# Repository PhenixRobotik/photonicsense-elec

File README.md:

# ultraphotonicsense-elec
Board for Time of Flight and ultrasonic sensors management

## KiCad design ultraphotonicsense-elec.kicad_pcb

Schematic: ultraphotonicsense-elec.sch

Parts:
C1, C2, C18, C19: 100n; C_0805_2012Metric_Pad1.15x1.40mm_HandSolder
J1: Conn_Debug; JST_PH_B6B-PH-K_1x06_P2.00mm_Vertical
JP1: Jumper_NC_Dual; PinHeader_1x03_P2.54mm_Vertical
LOGO1: Logo_Open_Hardware_Small; Logo_16,9mm
LOGO2: Logo_Open_Hardware_Small; OSHW-Logo2_7.3x6mm_SilkScreen
LOGO3: Logo_Open_Hardware_Small; KiCad-Logo_6mm_SilkScreen
MH1, MH2, MH3, MH4: MountingHole_Pad; MountingHole_2.2mm_M2_Pad
R1: 10k; R_0805_2012Metric_Pad1.15x1.40mm_HandSolder
U1: TXB0108PW; TSSOP-20_4.4x6.5mm_P0.65mm
U2: 74HC164; SOIC-14_3.9x8.7mm_P1.27mm
U8: TXB0104PW; TSSOP-14_4.4x5mm_P0.65mm

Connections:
+2V8: C19.2, U2.14, U8.1, U8.8; also elsewhere on the board
+3V3: C1.1, C18.2, JP1.3, U1.2, U8.14; also elsewhere on the board
+5V: JP1.1; also elsewhere on the board
/NRST_Logic/NRST: U8.11; also elsewhere on the board
/NRST_Logic/NRST_DBG: J1.2; also elsewhere on the board
/STM32F303K8/SWCLK: J1.3; also elsewhere on the board
/STM32F303K8/SWDIO: J1.4; also elsewhere on the board
/STM32F303K8/TOF_RESET_DATA: U8.13; also elsewhere on the board
/STM32F303K8/TOF_RESET_SHIFT: U8.12; also elsewhere on the board
/STM32F303K8/UART_RX: J1.5; also elsewhere on the board
/STM32F303K8/UART_TX: J1.6; also elsewhere on the board
/STM32F303K8/US_ECHO_0: U1.8; also elsewhere on the board
/STM32F303K8/US_ECHO_1: U1.6; also elsewhere on the board
/STM32F303K8/US_ECHO_2: U1.4; also elsewhere on the board
/STM32F303K8/US_ECHO_3: U1.1; also elsewhere on the board
/STM32F303K8/US_OE: R1.2, U1.10; also elsewhere on the board
/STM32F303K8/US_TRIG_0: U1.9; also elsewhere on the board
/STM32F303K8/US_TRIG_1: U1.7; also elsewhere on the board
/STM32F303K8/US_TRIG_2: U1.5; also elsewhere on the board
/STM32F303K8/US_TRIG_3: U1.3; also elsewhere on the board
/ToF_0/ToF_Reset: U2.3; also elsewhere on the board
/ToF_1/ToF_Reset: U2.4; also elsewhere on the board
/ToF_2/ToF_Reset: U2.5; also elsewhere on the board
/ToF_3/ToF_Reset: U2.6; also elsewhere on the board
/ToF_4/ToF_Reset: U2.10; also elsewhere on the board
/ToF_5/ToF_Reset: U2.11; also elsewhere on the board
/ToF_6/ToF_Reset: U2.12; also elsewhere on the board
/ToF_7/ToF_Reset: U2.13; also elsewhere on the board
/US_0/Echo: U1.13; also elsewhere on the board
/US_0/Trigger: U1.12; also elsewhere on the board
/US_1/Echo: U1.15; also elsewhere on the board
/US_1/Trigger: U1.14; also elsewhere on the board
/US_2/Echo: U1.17; also elsewhere on the board
/US_2/Trigger: U1.16; also elsewhere on the board
/US_3/Echo: U1.20; also elsewhere on the board
/US_3/Trigger: U1.18; also elsewhere on the board
GND: C1.2, C2.1, C18.1, C19.1, J1.1, MH1.1, MH2.1, MH3.1, MH4.1, R1.1, U1.11, U2.7, U8.7; also elsewhere on the board
unnamed: U2.1, U2.2, U8.2
unnamed: U2.8, U8.3
unnamed: U2.9, U8.4
US_PWR: C2.2, JP1.2, U1.19; also elsewhere on the board

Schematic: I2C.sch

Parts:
C20, C21: 100n; C_0805_2012Metric_Pad1.15x1.40mm_HandSolder
R2, R9, R10, R11: 10k; R_0805_2012Metric_Pad1.15x1.40mm_HandSolder
U9: TCA9517DR; TSSOP-8_3x3mm_P0.65mm

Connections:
+2V8: C20.2, R2.1, R9.1, U9.1; also elsewhere on the board
+3V3: C21.2, R10.1, R11.1, U9.8; also elsewhere on the board
/STM32F303K8/I2C_EN: U9.5; also elsewhere on the board
/STM32F303K8/I2C_SCL: R11.2, U9.7; also elsewhere on the board
/STM32F303K8/I2C_SDA: R10.2, U9.6; also elsewhere on the board
GND: C20.1, C21.1, U9.4; also elsewhere on the board
ToF_SCL: R2.2, U9.2; also elsewhere on the board
ToF_SDA: R9.2, U9.3; also elsewhere on the board

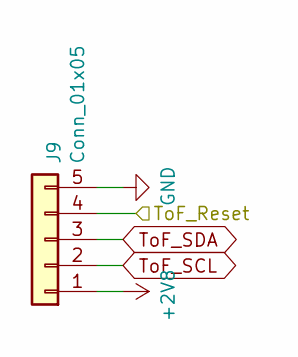
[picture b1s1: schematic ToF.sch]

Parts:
J5: Conn_01x05; JST_PH_B5B-PH-K_1x05_P2.00mm_Vertical

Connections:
+2V8: J5.1; also elsewhere on the board
/ToF_0/ToF_Reset: J5.4; also elsewhere on the board
GND: J5.5; also elsewhere on the board
ToF_SCL: J5.2; also elsewhere on the board
ToF_SDA: J5.3; also elsewhere on the board

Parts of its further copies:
J2, J3, J4, J6, J7, J8, J9: Conn_01x05; JST_PH_B5B-PH-K_1x05_P2.00mm_Vertical

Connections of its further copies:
+2V8: J2.1, J3.1, J4.1, J6.1, J7.1, J8.1, J9.1; also elsewhere on the board
/ToF_1/ToF_Reset: J2.4; also elsewhere on the board
/ToF_2/ToF_Reset: J3.4; also elsewhere on the board
/ToF_3/ToF_Reset: J4.4; also elsewhere on the board
/ToF_4/ToF_Reset: J6.4; also elsewhere on the board
/ToF_5/ToF_Reset: J7.4; also elsewhere on the board
/ToF_6/ToF_Reset: J8.4; also elsewhere on the board
/ToF_7/ToF_Reset: J9.4; also elsewhere on the board
GND: J2.5, J3.5, J4.5, J6.5, J7.5, J8.5, J9.5; also elsewhere on the board
ToF_SCL: J2.2, J3.2, J4.2, J6.2, J7.2, J8.2, J9.2; also elsewhere on the board
ToF_SDA: J2.3, J3.3, J4.3, J6.3, J7.3, J8.3, J9.3; also elsewhere on the board

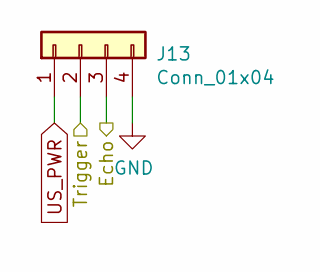
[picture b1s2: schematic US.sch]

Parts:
J10: Conn_01x04; JST_PH_B4B-PH-K_1x04_P2.00mm_Vertical

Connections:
/US_0/Echo: J10.3; also elsewhere on the board
/US_0/Trigger: J10.2; also elsewhere on the board
GND: J10.4; also elsewhere on the board
US_PWR: J10.1; also elsewhere on the board

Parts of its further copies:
J11, J12, J13: Conn_01x04; JST_PH_B4B-PH-K_1x04_P2.00mm_Vertical

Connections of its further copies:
/US_1/Echo: J11.3; also elsewhere on the board
/US_1/Trigger: J11.2; also elsewhere on the board
/US_2/Echo: J12.3; also elsewhere on the board
/US_2/Trigger: J12.2; also elsewhere on the board
/US_3/Echo: J13.3; also elsewhere on the board
/US_3/Trigger: J13.2; also elsewhere on the board
GND: J11.4, J12.4, J13.4; also elsewhere on the board
US_PWR: J11.1, J12.1, J13.1; also elsewhere on the board

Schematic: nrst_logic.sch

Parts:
C17: 100n; C_0805_2012Metric_Pad1.15x1.40mm_HandSolder
R12: 1k; R_0805_2012Metric_Pad1.15x1.40mm_HandSolder
R13, R14: 10k; R_0805_2012Metric_Pad1.15x1.40mm_HandSolder
SW1: SW_SPST; SW_SPST_CK_KSS_3.7x5.5mm
U10: SN74AHC1G08DBV; SOT-23-5_HandSoldering

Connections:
+3V3: R13.1, R14.1, U10.5; also elsewhere on the board
/NRST_Logic/NRST: U10.4; also elsewhere on the board
/NRST_Logic/NRST_DBG: R12.2, SW1.2; also elsewhere on the board
/Power_CAN/NRST: R13.2, U10.2; also elsewhere on the board
GND: C17.1, SW1.1, U10.3; also elsewhere on the board
unnamed: C17.2, R12.1, R14.2, U10.1

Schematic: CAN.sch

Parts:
C3, C4, C5: 100n; C_0805_2012Metric_Pad1.15x1.40mm_HandSolder
C6, C16: 10µ; CP_Elec_4x5.4
C7, C8: 1µ; C_0805_2012Metric_Pad1.15x1.40mm_HandSolder
D1: D; D_SMA
D2, D3, D4, D5: LED_ALT; LED_0805_2012Metric_Castellated
F1: Polyfusal; Fuse_1206_3216Metric_Pad1.42x1.75mm_HandSolder
P1, P2: CAN_conn; JST_XH_B05B-XH-A_1x05_P2.50mm_Vertical
R3: 700; R_0805_2012Metric_Pad1.15x1.40mm_HandSolder
R4: 500; R_0805_2012Metric_Pad1.15x1.40mm_HandSolder
R5: 330; R_0805_2012Metric_Pad1.15x1.40mm_HandSolder
R6: 6.8k; R_0805_2012Metric_Pad1.15x1.40mm_HandSolder
R7: 9.1k; R_0805_2012Metric_Pad1.15x1.40mm_HandSolder
R8: 280; R_0805_2012Metric_Pad1.15x1.40mm_HandSolder
U3: TCAN332; SOIC-8_3.9x4.9mm_P1.27mm
U4: LD1117S50TR_SOT223; SOT-223-3_TabPin2
U5: LD1117S33TR_SOT223; SOT-223-3_TabPin2
U6: LP38693MP-ADJ; SOT-223-5

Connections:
+2V8: C8.1, D5.2 (A), R7.1, U6.3; also elsewhere on the board
+3V3: C4.1, C7.2, C16.1, D4.2 (A), U3.3 (VCC), U5.2 (VO), U6.4; also elsewhere on the board
+5V: C5.1, C6.1, D3.2 (A), U4.2 (VO), U5.3 (VI); also elsewhere on the board
/Power_CAN/+7V_CAN: F1.2, P1.5, P2.5
/Power_CAN/NRST: P1.2, P2.2, U6.1; also elsewhere on the board
/STM32F303K8/CAN_RX: U3.4 (RXD); also elsewhere on the board
/STM32F303K8/CAN_TX: U3.1 (TXD); also elsewhere on the board
GND: C3.2, C4.2, C5.2, C6.2, C7.1, C8.2, C16.2, D1.2 (A), P1.1, P2.1, R3.2, R4.2, R5.2, R6.2, R8.2, U3.2 (GND), U4.1 (GND), U5.1 (GND), U6.5; also elsewhere on the board
unnamed: C3.1, D1.1 (K), D2.2 (A), F1.1, U4.3 (VI)
unnamed: D2.1 (K), R3.1
unnamed: D3.1 (K), R4.1
unnamed: D4.1 (K), R5.1
unnamed: D5.1 (K), R8.1
unnamed: P1.3, P2.3, U3.6 (CANL)
unnamed: P1.4, P2.4, U3.7 (CANH)
unnamed: R6.1, R7.2, U6.2

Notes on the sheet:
polarity and over current protection
VADJ = 1.25V pour VIN dans [3.2V, 10V] et IL dans ]100µA, 0.5A[ VOUT = VADJ * (1 + R1/R2) R1 <= 12k pour avoir 100µA R2 <= 100k pour limiter le bruit
R7 = 1.24*R6

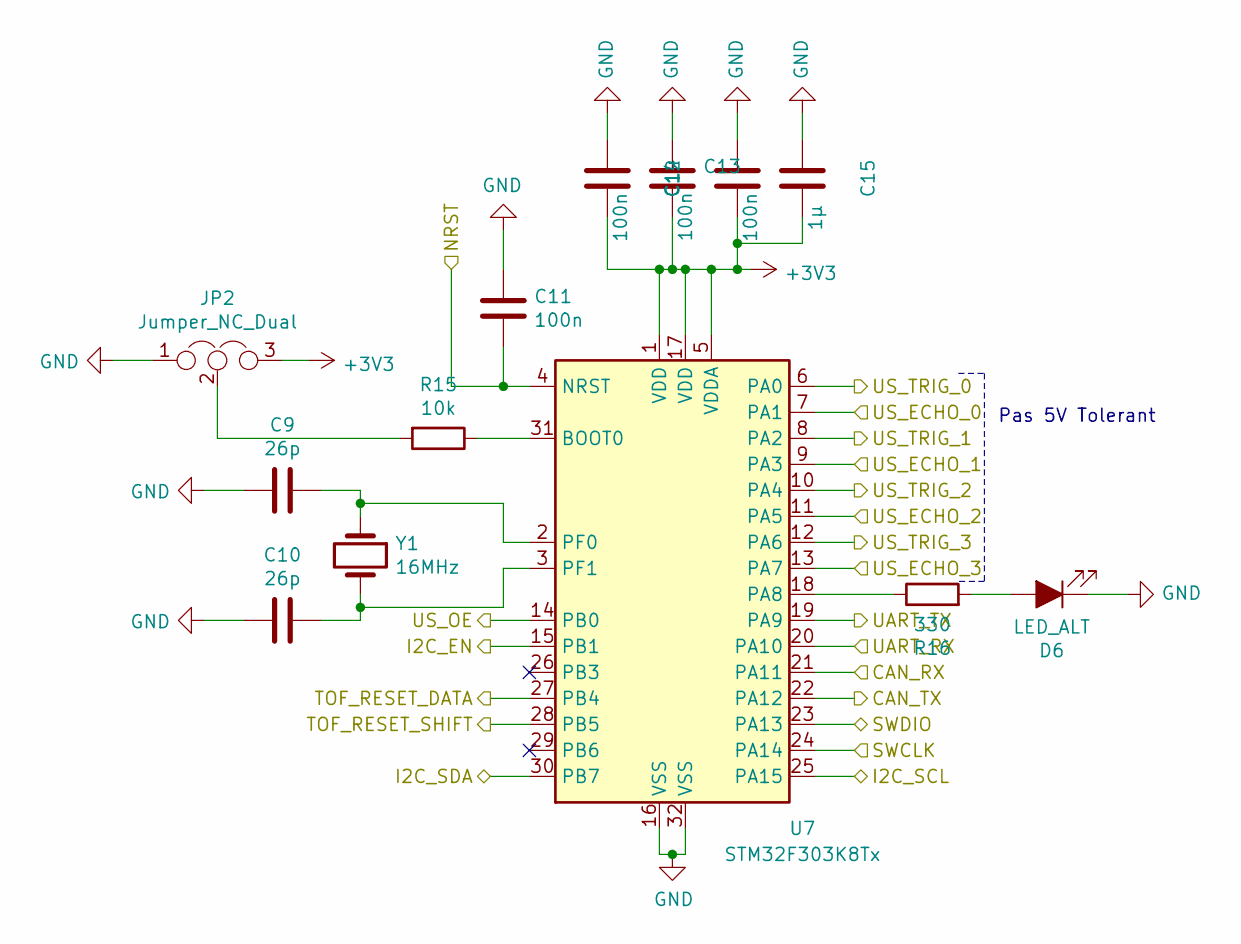
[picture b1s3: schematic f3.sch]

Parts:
C9, C10: 26p; C_0603_1608Metric_Pad1.05x0.95mm_HandSolder
C11, C12, C13, C14: 100n; C_0805_2012Metric_Pad1.15x1.40mm_HandSolder
C15: 1µ; C_0805_2012Metric_Pad1.15x1.40mm_HandSolder
D6: LED_ALT; LED_0805_2012Metric_Castellated
JP2: Jumper_NC_Dual; SolderJumper-3_P1.3mm_Open_RoundedPad1.0x1.5mm
R15: 10k; R_0805_2012Metric_Pad1.15x1.40mm_HandSolder
R16: 330; R_0805_2012Metric_Pad1.15x1.40mm_HandSolder
U7: STM32F303K8Tx; LQFP-32_7x7mm_P0.8mm
Y1: 16MHz; Crystal_HC49-4H_Vertical

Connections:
+3V3: C12.1, C13.2, C14.2, C15.1, JP2.3, U7.1 (VDD), U7.5 (VDDA), U7.17 (VDD); also elsewhere on the board
/NRST_Logic/NRST: C11.2, U7.4 (NRST); also elsewhere on the board
/STM32F303K8/CAN_RX: U7.21 (PA11); also elsewhere on the board
/STM32F303K8/CAN_TX: U7.22 (PA12); also elsewhere on the board
/STM32F303K8/I2C_EN: U7.15 (PB1); also elsewhere on the board
/STM32F303K8/I2C_SCL: U7.25 (PA15); also elsewhere on the board
/STM32F303K8/I2C_SDA: U7.30 (PB7); also elsewhere on the board
/STM32F303K8/SWCLK: U7.24 (PA14); also elsewhere on the board
/STM32F303K8/SWDIO: U7.23 (PA13); also elsewhere on the board
/STM32F303K8/TOF_RESET_DATA: U7.27 (PB4); also elsewhere on the board
/STM32F303K8/TOF_RESET_SHIFT: U7.28 (PB5); also elsewhere on the board
/STM32F303K8/UART_RX: U7.20 (PA10); also elsewhere on the board
/STM32F303K8/UART_TX: U7.19 (PA9); also elsewhere on the board
/STM32F303K8/US_ECHO_0: U7.7 (PA1); also elsewhere on the board
/STM32F303K8/US_ECHO_1: U7.9 (PA3); also elsewhere on the board
/STM32F303K8/US_ECHO_2: U7.11 (PA5); also elsewhere on the board
/STM32F303K8/US_ECHO_3: U7.13 (PA7); also elsewhere on the board
/STM32F303K8/US_OE: U7.14 (PB0); also elsewhere on the board
/STM32F303K8/US_TRIG_0: U7.6 (PA0); also elsewhere on the board
/STM32F303K8/US_TRIG_1: U7.8 (PA2); also elsewhere on the board
/STM32F303K8/US_TRIG_2: U7.10 (PA4); also elsewhere on the board
/STM32F303K8/US_TRIG_3: U7.12 (PA6); also elsewhere on the board
GND: C9.2, C10.2, C11.1, C12.2, C13.1, C14.1, C15.2, D6.1 (K), JP2.1, U7.16 (VSS), U7.32 (VSS); also elsewhere on the board
unnamed: C9.1, U7.2 (PF0), Y1.1
unnamed: C10.1, U7.3 (PF1), Y1.2
unnamed: D6.2 (A), R16.2
unnamed: JP2.2, R15.2
unnamed: R15.1, U7.31 (BOOT0)
unnamed: R16.1, U7.18 (PA8)

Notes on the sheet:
Pas 5V Tolerant

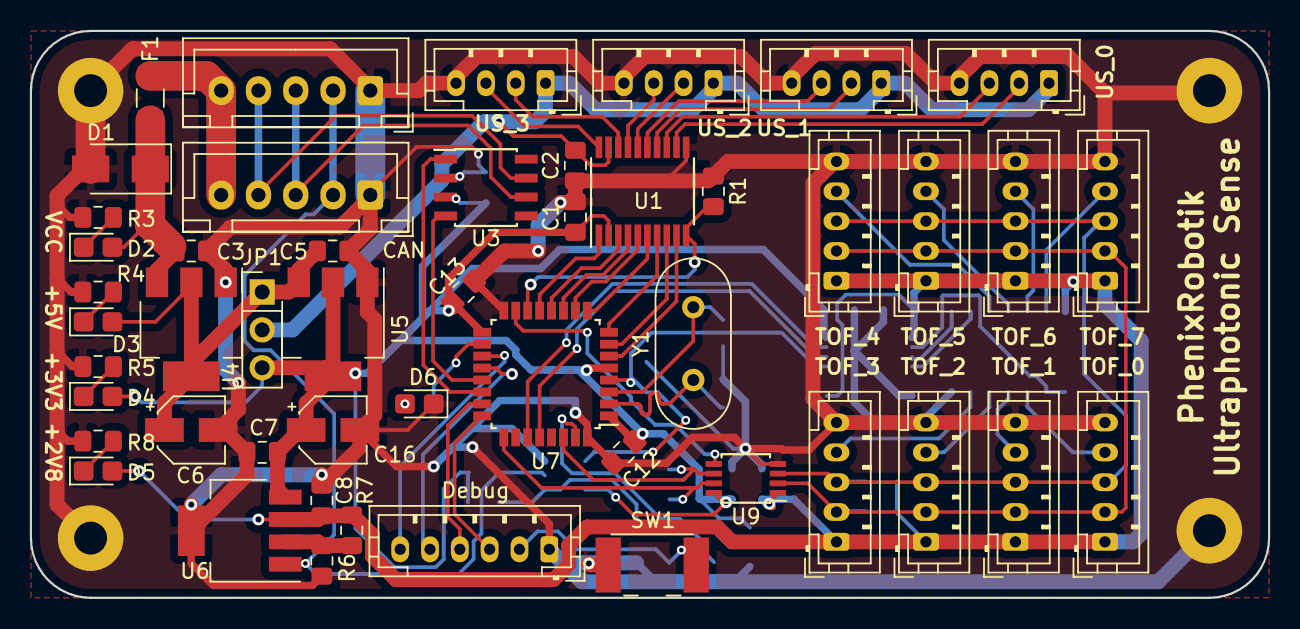
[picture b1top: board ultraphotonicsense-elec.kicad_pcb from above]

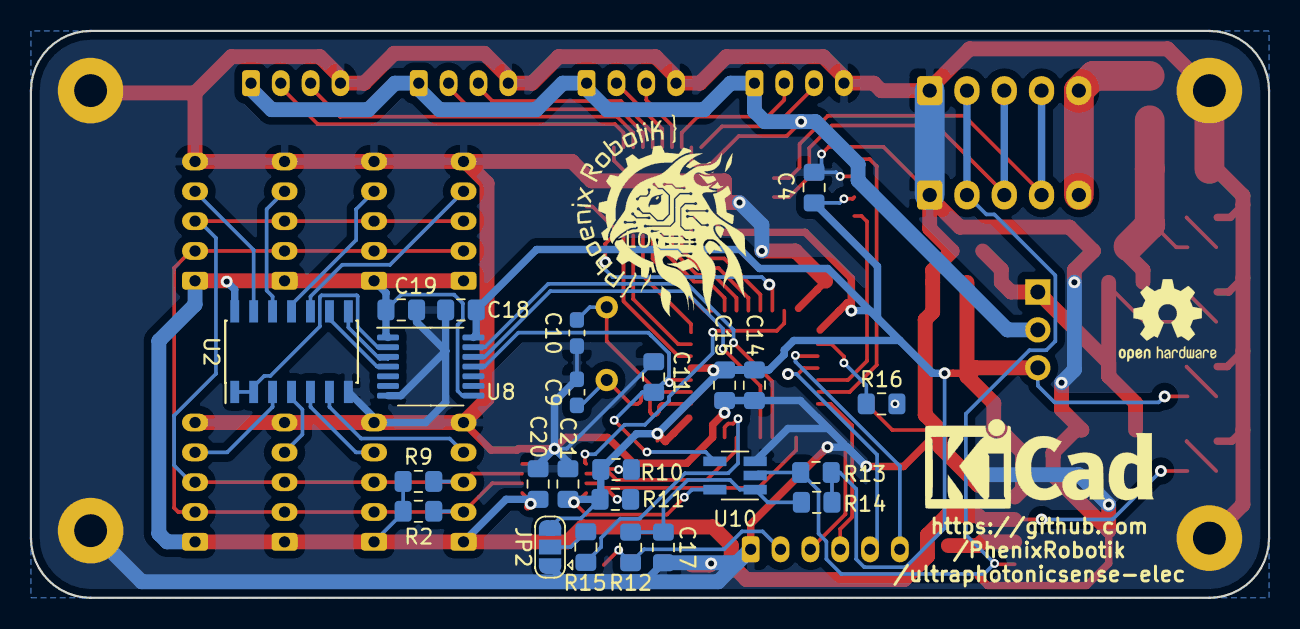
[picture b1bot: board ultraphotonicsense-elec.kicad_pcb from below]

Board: 2 copper layers, 83.0 x 38.0 mm, 80 parts (27 on the bottom side), 65 nets.

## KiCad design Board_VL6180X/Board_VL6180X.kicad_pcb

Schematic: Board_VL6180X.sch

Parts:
C1: 100nF; C_0805_2012Metric_Pad1.15x1.40mm_HandSolder
C2: 4.7µF; C_0805_2012Metric_Pad1.15x1.40mm_HandSolder
J1: Conn_01x06; JST_PH_S6B-PH-K_1x06_P2.00mm_Horizontal
JP3: SolderJumper_2_Open; SolderJumper-2_P1.3mm_Open_TrianglePad1.0x1.5mm
LOGO1: Logo_Open_Hardware_Small; OSHW-Logo2_7.3x6mm_SilkScreen
LOGO2: Logo_Open_Hardware_Small; Logo_8,5mm
MH1, MH2: MountingHole_Pad; MountingHole_2.2mm_M2_Pad
R1, R2: R; R_0805_2012Metric_Pad1.15x1.40mm_HandSolder
R3, R4: 47k; R_0805_2012Metric_Pad1.15x1.40mm_HandSolder
U1: VL6180X; ST_LGA-12_2.8x4.8x1.0mm_P0.75mm

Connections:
+2V8: C1.1, C2.2, J1.2, R1.2, R2.1, R3.1, R4.1, U1.8, U1.10
/GPIO: J1.1, JP3.2 (B), R4.2
/I2C_SCL: J1.3, R2.2, U1.5
/I2C_SDA: J1.4, R1.1, U1.6
/~XSHUT: J1.5, R3.2, U1.4
GND: C1.2, C2.1, J1.6, MH1.1, MH2.1, U1.9, U1.12
unnamed: JP3.1 (A), U1.1

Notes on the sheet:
Otionnel

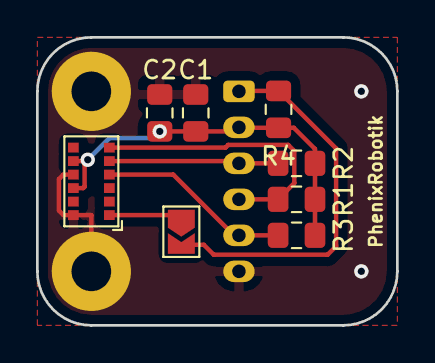
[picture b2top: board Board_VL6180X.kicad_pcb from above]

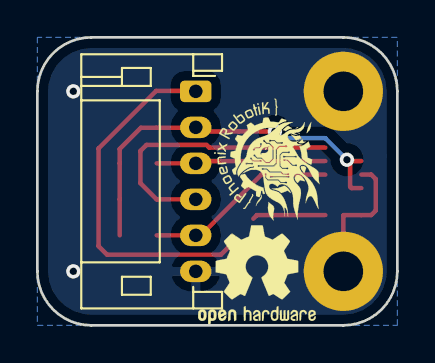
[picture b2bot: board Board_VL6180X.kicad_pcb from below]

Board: 2 copper layers, 20.0 x 16.0 mm, 13 parts (3 on the bottom side), 7 nets.

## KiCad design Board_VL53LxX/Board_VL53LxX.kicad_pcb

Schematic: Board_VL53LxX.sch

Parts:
C1: 100nF; C_0805_2012Metric_Pad1.15x1.40mm_HandSolder
C2: 4.7µF; C_0805_2012Metric_Pad1.15x1.40mm_HandSolder
J1: Conn_01x06; JST_PH_S6B-PH-K_1x06_P2.00mm_Horizontal
JP3: SolderJumper_2_Open; SolderJumper-2_P1.3mm_Open_TrianglePad1.0x1.5mm
LOGO1: Logo_Open_Hardware_Small; OSHW-Logo2_7.3x6mm_SilkScreen
LOGO2: Logo_Open_Hardware_Small; Logo_8,5mm
MH1, MH2: MountingHole_Pad; MountingHole_2.2mm_M2_Pad
R1, R2: R; R_0805_2012Metric_Pad1.15x1.40mm_HandSolder
R3, R4: 10k; R_0805_2012Metric_Pad1.15x1.40mm_HandSolder
U1: VL53L0X; TOF-12_4.4x2.4x1.0mm_P0.8mm

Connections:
+2V8: C1.1, C2.1, J1.2, R1.2, R2.1, R3.1, R4.1, U1.1
/GPIO: J1.1, JP3.2 (B), R4.2
/I2C_SCL: J1.3, R2.2, U1.3
/I2C_SDA: J1.4, R1.1, U1.2
/~XSHUT: J1.5, R3.2, U1.5
GND: C1.2, C2.2, J1.6, MH1.1, MH2.1, U1.4
unnamed: JP3.1 (A), U1.6

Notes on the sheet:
Otionnel

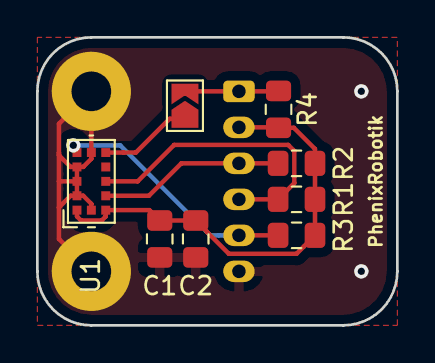
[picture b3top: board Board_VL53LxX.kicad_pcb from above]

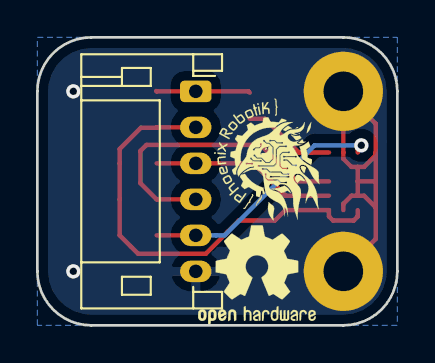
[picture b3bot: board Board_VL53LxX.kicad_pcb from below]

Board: 2 copper layers, 20.0 x 16.0 mm, 13 parts (3 on the bottom side), 7 nets.

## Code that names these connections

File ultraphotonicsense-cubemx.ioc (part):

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PF0\ /\ OSC_IN.Mode=HSE-External-Oscillator
Mcu.UserName=STM32F303K8Tx
RCC.SYSCLKSourceVirtual=RCC_SYSCLKSOURCE_PLLCLK
PA0.GPIO_Label=US_TRIG_0
PA9.GPIOParameters=GPIO_Label
PA11.Mode=Master
PA3.GPIOParameters=GPIO_Label
PA6.GPIO_Label=US_TRIG_3
PB0.GPIO_Label=US_OUTPUT_ENABLE
RCC.HSEPLLFreq_Value=16000000
PA2.GPIOParameters=GPIO_Label
PB5.GPIOParameters=GPIO_Label
PA15.GPIO_Label=I2C1_SCL_ToF
PB4.GPIOParameters=GPIO_Label
PA12.Signal=CAN_TX
PA8.GPIOParameters=GPIO_Label
RCC.HSE_VALUE=16000000
PA15.Mode=I2C
PB0.GPIOParameters=GPIO_Label
PA1.GPIOParameters=GPIO_Label
PA14.Mode=Serial_Wire
PB1.GPIO_Label=I2C_TOF_EN
PA10.GPIO_Label=USART1_RX_DEBUG
PB7.Signal=I2C1_SDA
PA8.Signal=GPIO_Output
PA0.Signal=GPIO_Output
PB7.GPIO_Label=I2C1_SDA_ToF
Mcu.Package=LQFP32
PB1.Signal=GPIO_Output
PA6.Signal=GPIO_Output
PA2.GPIO_Label=US_TRIG_1
PA10.Signal=USART1_RX
PA15.Signal=I2C1_SCL
PA5.GPIOParameters=GPIO_Label
PB5.GPIO_Label=TOF_RESET_SHIFT
PA4.GPIO_Label=US_TRIG_2
PB4.Signal=GPIO_Output
PA3.Signal=GPXTI3
PA6.GPIOParameters=GPIO_Label
PA10.Mode=Asynchronous
PA15.GPIOParameters=GPIO_Label
PA9.GPIO_Label=USART1_TX_DEBUG
PA13.Signal=SYS_JTMS-SWDIO
PA9.Mode=Asynchronous
PA8.GPIO_Label=LED_Status
PB7.GPIOParameters=GPIO_Label
PA9.Signal=USART1_TX
PA1.Signal=GPXTI1
PF1\ /\ OSC_OUT.Signal=RCC_OSC_OUT
PA5.Signal=GPXTI5
board=custom
PF0\ /\ OSC_IN.Signal=RCC_OSC_IN
PB4.GPIO_Label=TOF_RESET_DATA
PA1.GPIO_Label=US_ECHO_0 [INT]
PA10.GPIOParameters=GPIO_Label
PA4.GPIOParameters=GPIO_Label
PA13.Mode=Serial_Wire
Mcu.Name=STM32F303K(6-8)Tx
PA2.Signal=GPIO_Output
PA4.Signal=GPIO_Output
RCC.SYSCLKFreq_VALUE=64000000
PB5.Signal=GPIO_Output
PA7.GPIO_Label=US_ECHO_3 [INT]
PA12.Mode=Master
PA5.GPIO_Label=US_ECHO_2 [INT]
PB7.Mode=I2C
PA11.Signal=CAN_RX
PA14.Signal=SYS_JTCK-SWCLK
PA0.GPIOParameters=GPIO_Label
PB0.Signal=GPIO_Output
PA7.GPIOParameters=GPIO_Label
PF1\ /\ OSC_OUT.Mode=HSE-External-Oscillator
PA3.GPIO_Label=US_ECHO_1 [INT]
PB1.GPIOParameters=GPIO_Label
PA7.Signal=GPXTI7

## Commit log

2018-10-08 Added phenix_kicad submodule
2018-10-08 KiCad gitignore
2018-10-08 CubeMX project for pins configuration
2018-10-08 Scheme : power and CPU
2018-10-08 Added I2C level shifter
2018-10-08 Added ToF connectors and fixed schematic ERC
2018-10-09 Fixed ToF Reset levels
2018-10-10 Update library submodule
2018-10-10 New GPIO config
2018-10-10 Update gitignore
2018-10-10 Update F3 for ultrasonic sensors and shift register
2018-10-10 Deleted ToF reset level shifter
2018-10-10 Added ultrasonic sensors
2018-10-10 Added power selector for ultrasonic sensors
2018-10-10 Minor detail in cubemx project
2018-10-10 Rename project
2018-10-10 Added mounting holes
2018-10-10 Fixed shift register voltage translation
2018-10-10 Added interrupt descriptions to cubemx project
2018-10-10 Fixed TTa pins issue
2018-10-11 Added IC for level translation with ultrasonic sensors
2018-10-11 Added ultrasonic sensors power selection
2018-10-12 Footprint association
2018-10-13 Schematic corrections
2018-10-13 Placement done
2018-10-14 PCB routed, no errors but still a few tracks too close
2018-10-14 Improved tracks spacing
2018-10-14 Added VL53LxX board schematics
2018-10-14 VL53L board routed
2018-10-21 Corrected, routing redone
2018-10-23 Improved a few tracks
2018-10-28 Update VL53L0X PCB
2018-10-28 Added Board VL6180X schematics
2018-10-28 PCB VL6180X done
2018-10-28 Changed JST connectors
2018-11-01 update gitignore and phenix_kicad. Remove ignored files.
2018-11-01 update sym libs
2018-11-04 Added RS refs
2018-11-04 Update phenix_kicadé
2018-11-04 Improved text placement
2018-11-04 Added component values
2018-11-05 Rename phoenix phenix. Connect mounting holes to gnd.
2018-11-05 fix drc
2018-11-05 update from schema
2018-11-05 cleanup
2018-11-05 small fixes
2018-11-05 update board
2018-11-05 add logos
2018-11-12 Changed connector orientation, better capacitance positionning, cleaner pcb
2019-02-05 Added resistors values
2020-10-03 Updated phenix_kicad library
2020-10-03 Updated schematics
2020-10-03 Update gitignore for sch-bak
2020-10-04 Update PCB
2020-10-04 Update silkscreen
2020-10-17 Updated I2C schematic comments and IOC for clock configuration
2020-10-17 Added optional pull-up on UART TX
